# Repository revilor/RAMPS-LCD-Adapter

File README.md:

# RAMPS-LCD-Adapter

This is an adapter to free pins 16 and 17 on the RAMPS AUX-4 connector usually used for LCDs to be used for the MMU2 serial connection. The LCD I use is the Anet 12864 LCD Smart Display Controller. Other LCDs might work but I can't guarantee for that.

## Marlin 2.0 settings for Anet LCD

To use the Anet LCD with this adapter you have to set the following configuration options in Marlin.

### Configuration.h

```
#define REPRAP_DISCOUNT_FULL_GRAPHIC_SMART_CONTROLLER
```

### pins_RAMPS.h

At the end of the file add

```
// custom pins ANET LCD 12864

#undef LCD_PINS_RS
#undef LCD_PINS_ENABLE
#undef LCD_PINS_D4
#undef LCD_PINS_D5
#undef LCD_PINS_D6
#undef LCD_PINS_D7
#undef BEEPER_PIN

#define LCD_PINS_RS     25
#define LCD_PINS_ENABLE 27
#define LCD_PINS_D4     29
#define LCD_PINS_D5     -1
#define LCD_PINS_D6     -1
#define LCD_PINS_D7     -1
#define BEEPER_PIN        37

#define STD_ENCODER_PULSES_PER_STEP 4
#define STD_ENCODER_STEPS_PER_MENU_ITEM 1

//#define ST7920_DELAY_1 DELAY_1_NOP
//#define ST7920_DELAY_2 DELAY_2_NOP
//#define ST7920_DELAY_3 DELAY_3_NOP

#define ST7920_DELAY_1 DELAY_NS(0)
#define ST7920_DELAY_2 DELAY_NS(63)
#define ST7920_DELAY_3 DELAY_NS(125)
```

## MMU2 connector

The MMU2 connector has the following pins from top to bottom (colors correspond to the original Prusa MMU2 serial cable):

 * +5V (Blue)
 * TX (White)
 * RX (Green)
 * NC
 * Hardware Reset (Brown)

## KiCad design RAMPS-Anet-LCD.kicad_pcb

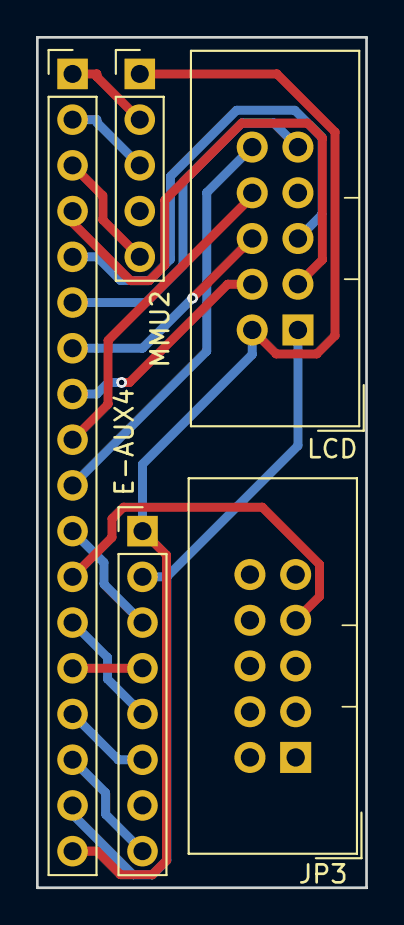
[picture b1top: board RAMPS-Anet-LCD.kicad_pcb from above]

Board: 2 copper layers, 18.3 x 47.2 mm, 5 parts (0 on the bottom side), 18 nets.

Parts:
J1: E-AUX4; PinHeader_1x08_P2.54mm_Vertical
J2: LCD; IDC-Header_2x05_P2.54mm_Vertical
J3: JP3; IDC-Header_2x05_P2.54mm_Vertical
J4: MMU2; Pin_Header_Straight_1x05_Pitch2.54mm
J5: AUX-4; Pin_Header_Straight_1x18_Pitch2.54mm

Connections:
+5V: J1.1, J2.2, J4.1, J5.18
/Brown: J4.5, J5.3
/D16: J4.2, J5.1
/D17: J4.3, J5.2
/D25: J2.3, J5.4
/D27: J2.5, J5.5
/D29: J2.9, J5.6
/D31: J2.6, J5.7
/D32: J1.8, J5.16
/D33: J2.4, J5.8
/D35: J2.8, J5.9
/D37: J2.10, J5.10
/D39: J1.3, J5.11
/D41: J3.7, J5.12
/D43: J1.5, J5.13
/D45: J1.4, J5.14
/D47: J1.6, J5.15
GND: J1.2, J2.1, J5.17

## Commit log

2019-04-11 MMU2 connector description
